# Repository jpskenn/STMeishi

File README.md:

# STMeishi
STM32F303CCT6 based evaluation keyboard in Meishi (= name card).

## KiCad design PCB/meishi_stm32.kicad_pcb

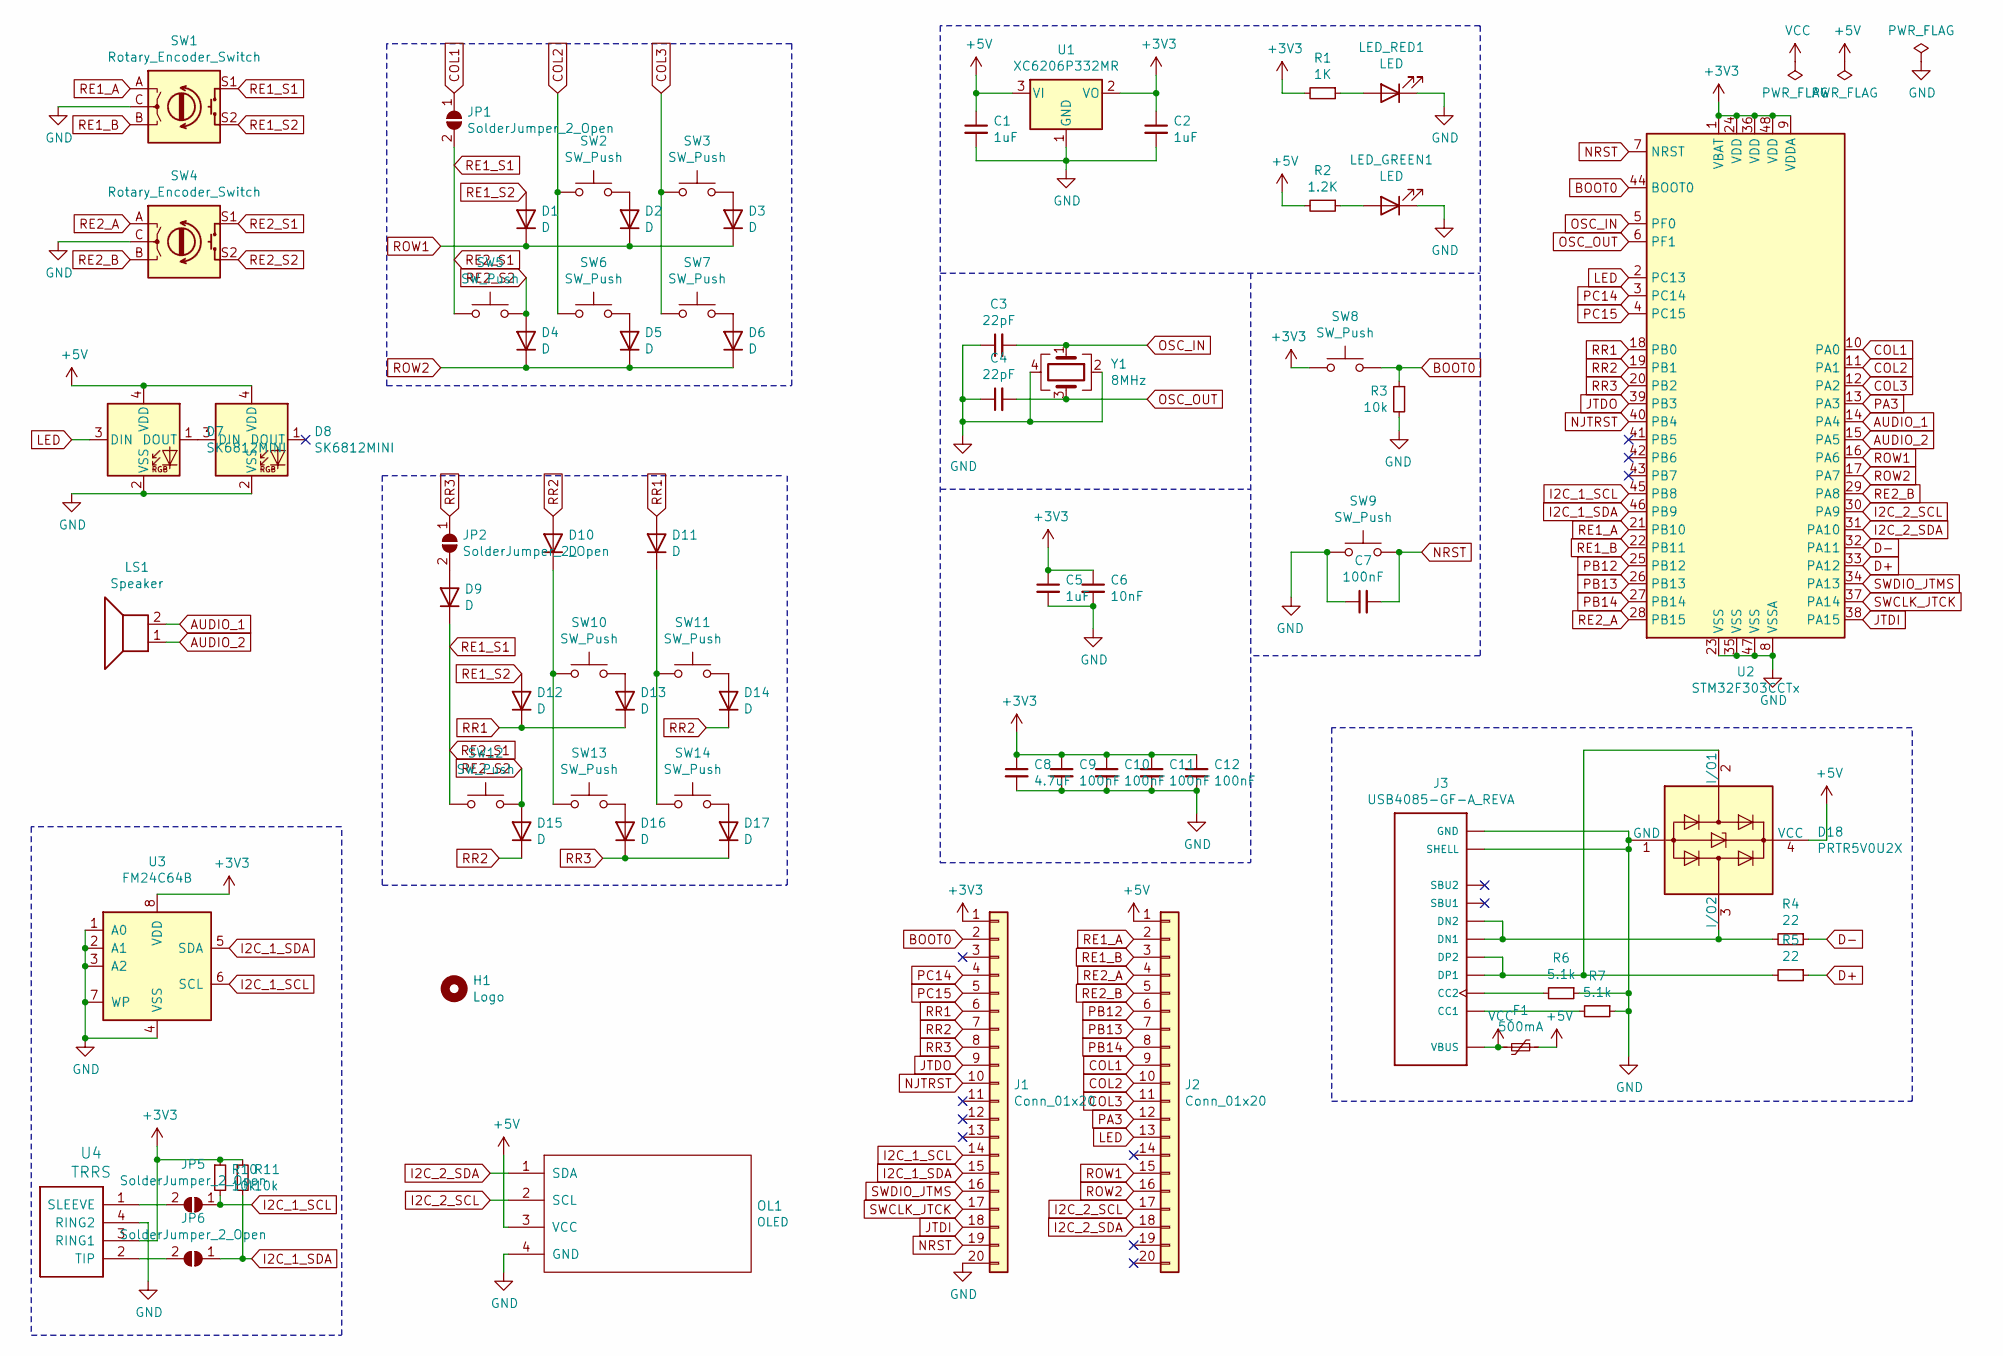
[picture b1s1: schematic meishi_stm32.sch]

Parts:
C1, C2, C5: 1uF; C_0805_2012Metric_Pad1.15x1.40mm_HandSolder; LCSC Part # C28323
C3, C4: 22pF; C_0805_2012Metric_Pad1.15x1.40mm_HandSolder; LCSC Part # C1804
C6: 10nF; C_0805_2012Metric_Pad1.15x1.40mm_HandSolder; LCSC Part # C15850
C7, C9, C10, C11, C12: 100nF; C_0805_2012Metric_Pad1.15x1.40mm_HandSolder; LCSC Part # C49678
C8: 4.7uF; C_0805_2012Metric_Pad1.15x1.40mm_HandSolder; LCSC Part # C1779
D1, D2, D3, D4, D5, D6, D9, D10, D11, D12, D13, D14, D15, D16, D17: D; D_SOD-123; LCSC Part # C81598
D7, D8: SK6812MINI; LED_SK6812MINI_PLCC4_3.5x3.5mm_P1.75mm
D18: PRTR5V0U2X; SOT-143; LCSC Part # C78442
F1: 500mA; Fuse_1206_3216Metric_Pad1.42x1.75mm_HandSolder; LCSC Part # C70076
H1: Logo; st_meishi_logo_475dpi
J1, J2: Conn_01x20; PinHeader_1x20_P2.54mm_Vertical
J3: USB4085-GF-A_REVA; USB_C_Receptacle_GCT_USB4085_pad_modified
JP1, JP2: SolderJumper_2_Open; PinHeader_1x02_P2.54mm_Vertical
JP5, JP6: SolderJumper_2_Open; SolderJumper-2_P1.3mm_Open_Pad1.0x1.5mm
LED_GREEN1: LED; LED_D4.0mm
LED_RED1: LED; LED_D4.0mm
LS1: Speaker; Buzzer_Murata_PKMCS0909E4000-R1
OL1: OLED
R1: 1K; R_0805_2012Metric_Pad1.15x1.40mm_HandSolder; LCSC Part # C17513
R2: 1.2K; R_0805_2012Metric_Pad1.15x1.40mm_HandSolder; LCSC Part # C17379
R3: 10k; R_0805_2012Metric_Pad1.15x1.40mm_HandSolder; LCSC Part # C17414
R4, R5: 22; R_0805_2012Metric_Pad1.15x1.40mm_HandSolder; LCSC Part # C17561
R6, R7: 5.1k; R_0805_2012Metric_Pad1.15x1.40mm_HandSolder; LCSC Part # C27834
R10, R11: 10k; Resistor-Hybrid-Front; LCSC Part # C17414
SW1, SW4: Rotary_Encoder_Switch; RotaryEncoder_Alps_EC11E-Switch_Vertical_H20mm
SW2, SW3, SW5, SW6, SW7: SW_Push; MXOnly-1U-Hotswap
SW8, SW9: SW_Push; ResetSW_1side
SW10, SW11, SW12, SW13, SW14: SW_Push; Choc_Hotswap_single_side
U1: XC6206P332MR; SOT-23; LCSC Part # C5446
U2: STM32F303CCTx; LQFP-48_7x7mm_P0.5mm; LCSC Part # C81523
U3: FM24C64B; SOIC-8_3.9x4.9mm_P1.27mm; LCSC Part # C79988
U4: TRRS; CON_MJ-4PP-9
Y1: 8MHz; Crystal_SMD_3225-4Pin_3.2x2.5mm_HandSoldering; LCSC Part # C57131

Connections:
+3V3: C2.1, C5.1, C6.1, C8.1, C9.1, C10.1, C11.1, C12.1, J1.1, R1.2, R10.1, R11.1, SW8.2, U1.2 (VO), U2.1 (VBAT), U2.9 (VDDA), U2.24 (VDD), U2.36 (VDD), U2.48 (VDD), U3.8 (VDD), U4.3 (RING1)
+5V: C1.1, D7.4 (VDD), D8.4 (VDD), D18.4 (VCC), F1.1, J2.1, OL1.3 (VCC), R2.2, U1.3 (VI)
AUDIO_1: LS1.2, U2.14 (PA4)
AUDIO_2: LS1.1, U2.15 (PA5)
BOOT0: J1.2, R3.1, SW8.1, U2.44 (BOOT0)
COL1: J2.9, JP1.1 (A), U2.10 (PA0)
COL2: J2.10, SW2.1, SW6.1, U2.11 (PA1)
COL3: J2.11, SW3.1, SW7.1, U2.12 (PA2)
D+: R5.1, U2.33 (PA12)
D-: R4.1, U2.32 (PA11)
GND: C1.2, C2.2, C3.1, C4.1, C5.2, C6.2, C7.1, C8.2, C9.2, C10.2, C11.2, C12.2, D7.2 (VSS), D8.2 (VSS), D18.1 (GND), J1.20, J3.A1 (GND), J3.A12 (GND), J3.B1 (GND), J3.B12 (GND), J3.P1 (SHELL), J3.P2 (SHELL), J3.P3 (SHELL), J3.P4 (SHELL), LED_GREEN1.1 (K), LED_RED1.1 (K), OL1.4 (GND), R3.2, R6.1, R7.1, SW1.C, SW4.C, SW9.2, U1.1 (GND), U2.8 (VSSA), U2.23 (VSS), U2.35 (VSS), U2.47 (VSS), U3.1 (A0), U3.2 (A1), U3.3 (A2), U3.4 (VSS), U3.7 (WP), U4.4 (RING2), Y1.2, Y1.4
I2C_1_SCL: J1.14, JP5.1 (A), R10.2, U2.45 (PB8), U3.6 (SCL)
I2C_1_SDA: J1.15, JP6.1 (A), R11.2, U2.46 (PB9), U3.5 (SDA)
I2C_2_SCL: J2.17, OL1.2 (SCL), U2.30 (PA9)
I2C_2_SDA: J2.18, OL1.1 (SDA), U2.31 (PA10)
JTDI: J1.18, U2.38 (PA15)
JTDO: J1.9, U2.39 (PB3)
LED: D7.3 (DIN), J2.13, U2.2 (PC13)
NJTRST: J1.10, U2.40 (PB4)
NRST: C7.2, J1.19, SW9.1, U2.7 (NRST)
unnamed: D2.2 (A), SW2.2
unnamed: D3.2 (A), SW3.2
unnamed: D5.2 (A), SW6.2
unnamed: D6.2 (A), SW7.2
unnamed: D7.1 (DOUT), D8.3 (DIN)
unnamed: D9.2 (A), JP2.2 (B)
unnamed: D10.1 (K), SW10.1, SW13.1
unnamed: D11.1 (K), SW11.1, SW14.1
unnamed: D13.2 (A), SW10.2
unnamed: D14.2 (A), SW11.2
unnamed: D16.2 (A), SW13.2
unnamed: D17.2 (A), SW14.2
unnamed: D18.2 (I/O1), J3.A6 (DP1), J3.B6 (DP2), R5.2
unnamed: D18.3 (I/O2), J3.A7 (DN1), J3.B7 (DN2), R4.2
unnamed: J3.A5 (CC1), R7.2
unnamed: J3.B5 (CC2), R6.2
unnamed: JP5.2 (B), U4.1 (SLEEVE)
unnamed: JP6.2 (B), U4.2 (TIP)
unnamed: LED_GREEN1.2 (A), R2.1
unnamed: LED_RED1.2 (A), R1.1
OSC_IN: C3.2, U2.5 (PF0), Y1.1
OSC_OUT: C4.2, U2.6 (PF1), Y1.3
PA3: J2.12, U2.13 (PA3)
PB12: J2.6, U2.25 (PB12)
PB13: J2.7, U2.26 (PB13)
PB14: J2.8, U2.27 (PB14)
PC14: J1.4, U2.3 (PC14)
PC15: J1.5, U2.4 (PC15)
RE1_A: J2.2, SW1.A, U2.21 (PB10)
RE1_B: J2.3, SW1.B, U2.22 (PB11)
RE1_S1: D9.1 (K), JP1.2 (B), SW1.S1, SW4.S1, SW5.1, SW12.1
RE1_S2: D1.2 (A), D12.2 (A), SW1.S2
RE2_A: J2.4, SW4.A, U2.28 (PB15)
RE2_B: J2.5, SW4.B, U2.29 (PA8)
RE2_S2: D4.2 (A), D15.2 (A), SW4.S2, SW5.2, SW12.2
ROW1: D1.1 (K), D2.1 (K), D3.1 (K), J2.15, U2.16 (PA6)
ROW2: D4.1 (K), D5.1 (K), D6.1 (K), J2.16, U2.17 (PA7)
RR1: D11.2 (A), D12.1 (K), D13.1 (K), J1.6, U2.18 (PB0)
RR2: D10.2 (A), D14.1 (K), D15.1 (K), J1.7, U2.19 (PB1)
RR3: D16.1 (K), D17.1 (K), J1.8, JP2.1 (A), U2.20 (PB2)
SWCLK_JTCK: J1.17, U2.37 (PA14)
SWDIO_JTMS: J1.16, U2.34 (PA13)
VCC: F1.2, J3.A4 (VBUS), J3.A9 (VBUS), J3.B4 (VBUS), J3.B9 (VBUS)

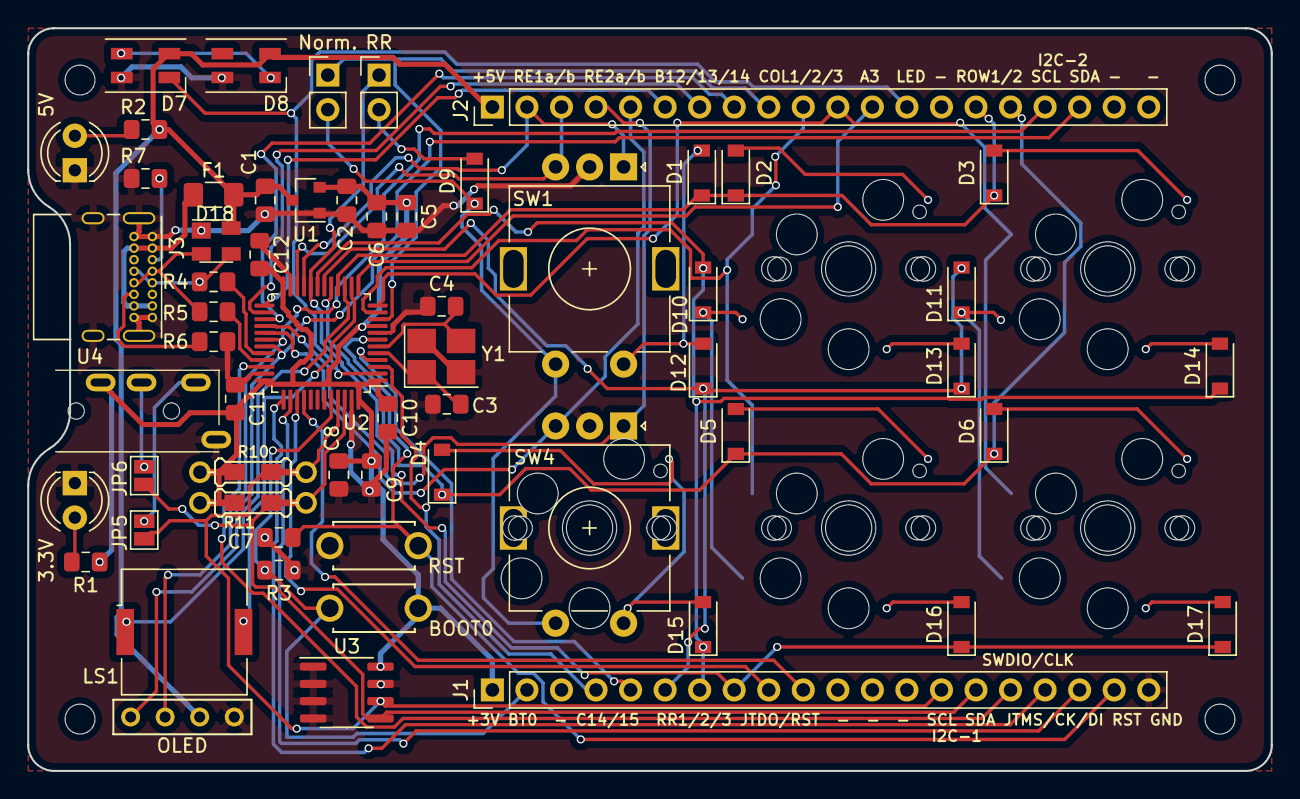
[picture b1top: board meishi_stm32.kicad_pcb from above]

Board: 2 copper layers, 91.4 x 54.6 mm, 71 parts (1 on the bottom side), 63 nets.

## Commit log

2020-10-25 New v.1基板と画像など
